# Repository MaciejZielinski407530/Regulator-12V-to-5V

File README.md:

**Regulator napięcia 12V do 5V**

Regulator napięcia 12V do 5V dla zasilania modułu audio Bluetooth-AUX.
Moduł audio do zastosowania w pojazdach bez wbudowanej funkcji Bluetooth.
Radio musi posiadać wejście AUX.

Moduł zasilany napięciem 5V co wymaga obniżenia typowego napięcia w pojazdach (12V).
Wymiary PCB identyczne do wymiarów modułu audio.
Moduł audio oraz regulator zostały spiętrowane i zamknięte w obudowie z drukarki 3D.

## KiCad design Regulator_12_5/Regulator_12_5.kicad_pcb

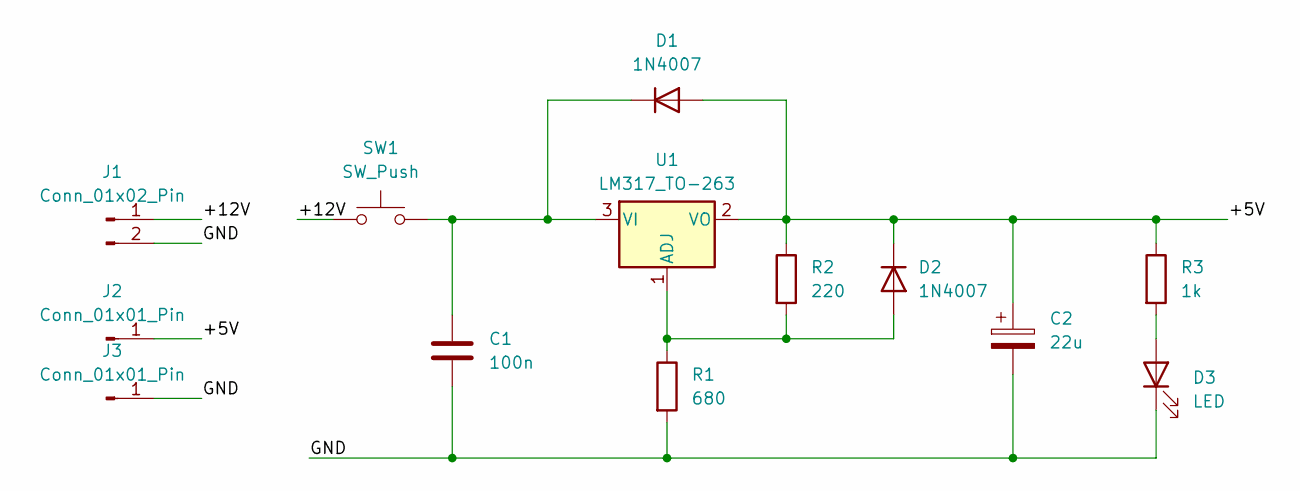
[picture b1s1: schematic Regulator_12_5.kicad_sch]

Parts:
C1: 100n; C_Disc_D8.0mm_W5.0mm_P5.00mm
C2: 22u; CP_Radial_D5.0mm_P2.00mm
D1, D2: 1N4007; D_A-405_P10.16mm_Horizontal
D3: LED; LED_D5.0mm
J1: Conn_01x02_Pin; Altech_AK100_1x02_P5.00mm
J2, J3: Conn_01x01_Pin; PinHeader_1x01_P2.54mm_Vertical
R1: 680; R_0805_2012Metric_Pad1.20x1.40mm_HandSolder
R2: 220; R_0805_2012Metric_Pad1.20x1.40mm_HandSolder
R3: 1k; R_1206_3216Metric_Pad1.30x1.75mm_HandSolder
SW1: SW_Push; SW_Push_2P2T_Toggle_CK_PVA2xxH3xxxxxxV2
U1: LM317_TO-263; TO-263-2

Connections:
/+5V: C2.1, D1.2 (A), D2.1 (K), J2.1, R2.1, R3.1, U1.2 (VO)
/+12V: J1.1, SW1.1
/GND: C1.2, C2.2, D3.1 (K), J1.2, J3.1, R1.2
unnamed: C1.1, D1.1 (K), SW1.2, U1.3 (VI)
unnamed: D2.2 (A), R1.1, R2.2, U1.1 (ADJ)
unnamed: D3.2 (A), R3.2

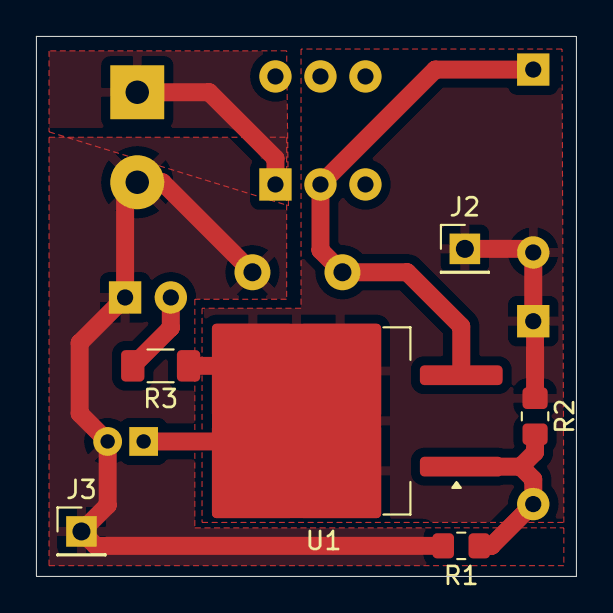
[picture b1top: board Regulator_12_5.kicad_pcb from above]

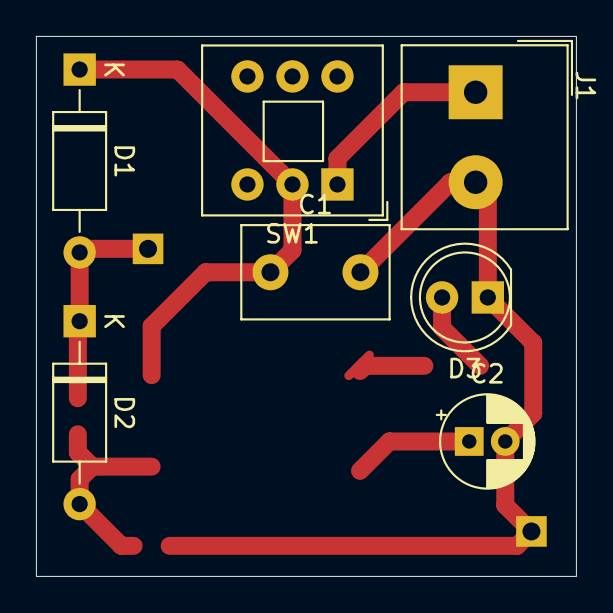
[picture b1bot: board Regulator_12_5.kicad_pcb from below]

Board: 2 copper layers, 30.0 x 30.0 mm, 13 parts (7 on the bottom side), 6 nets.
